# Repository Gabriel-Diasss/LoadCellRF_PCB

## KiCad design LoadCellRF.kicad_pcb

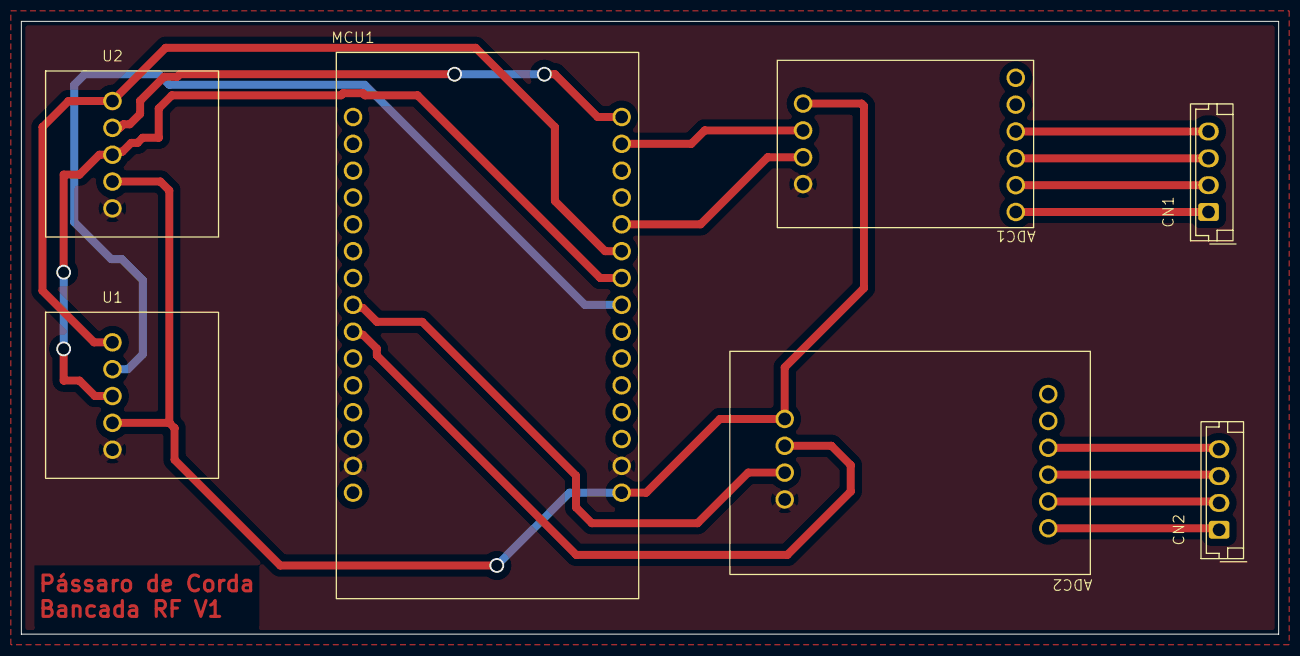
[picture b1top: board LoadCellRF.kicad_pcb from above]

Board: 2 copper layers, 119.0 x 58.0 mm, 7 parts (0 on the bottom side), 18 nets.

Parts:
ADC1: HX711_240X156
ADC2: HX711_339X209
CN1, CN2: JST_EH_B4B-EH-A_1x04_P2.54mm_Vertical
MCU1: ESP32 ESP-WROOM-32 DEVKit V1
U1, U2: MAX6675_DIAS

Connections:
+3.3V: ADC1.10 (VCC), ADC2.10 (VCC), MCU1.30 (3V3), U1.4 (V_{CC}), U2.4 (V_{CC})
/A+(S+)1: ADC1.4 (A+), CN1.4
/A+(S+)2: ADC2.4 (A+), CN2.4
/A-(s-)1: ADC1.3 (A-), CN1.3
/A-(s-)2: ADC2.3 (A-), CN2.3
/CS1: MCU1.23 (D5), U1.2 (~CS)
/CS2: MCU1.16 (D23), U2.2 (~CS)
/DT1: ADC1.8 (DT), MCU1.20 (D21)
/DT2: ADC2.8 (DT), MCU1.8 (D25)
/E+1: ADC1.1 (E+), CN1.1
/E+2: ADC2.1 (E+), CN2.1
/E-1: ADC1.2 (E-), CN1.2
/E-2: ADC2.2 (E-), CN2.2
/SCK: MCU1.22 (D18), U1.3 (SCK), U2.3 (SCK)
/SCK1: ADC1.9 (SCK), MCU1.17 (D22)
/SCK2: ADC2.9 (SCK), MCU1.9 (D26)
/SO: MCU1.21 (D19), U1.1 (SO), U2.1 (SO)
GND: ADC1.7 (GND), ADC2.7 (GND), MCU1.14 (GND), MCU1.29 (GND), U1.5 (GND), U2.5 (GND)
